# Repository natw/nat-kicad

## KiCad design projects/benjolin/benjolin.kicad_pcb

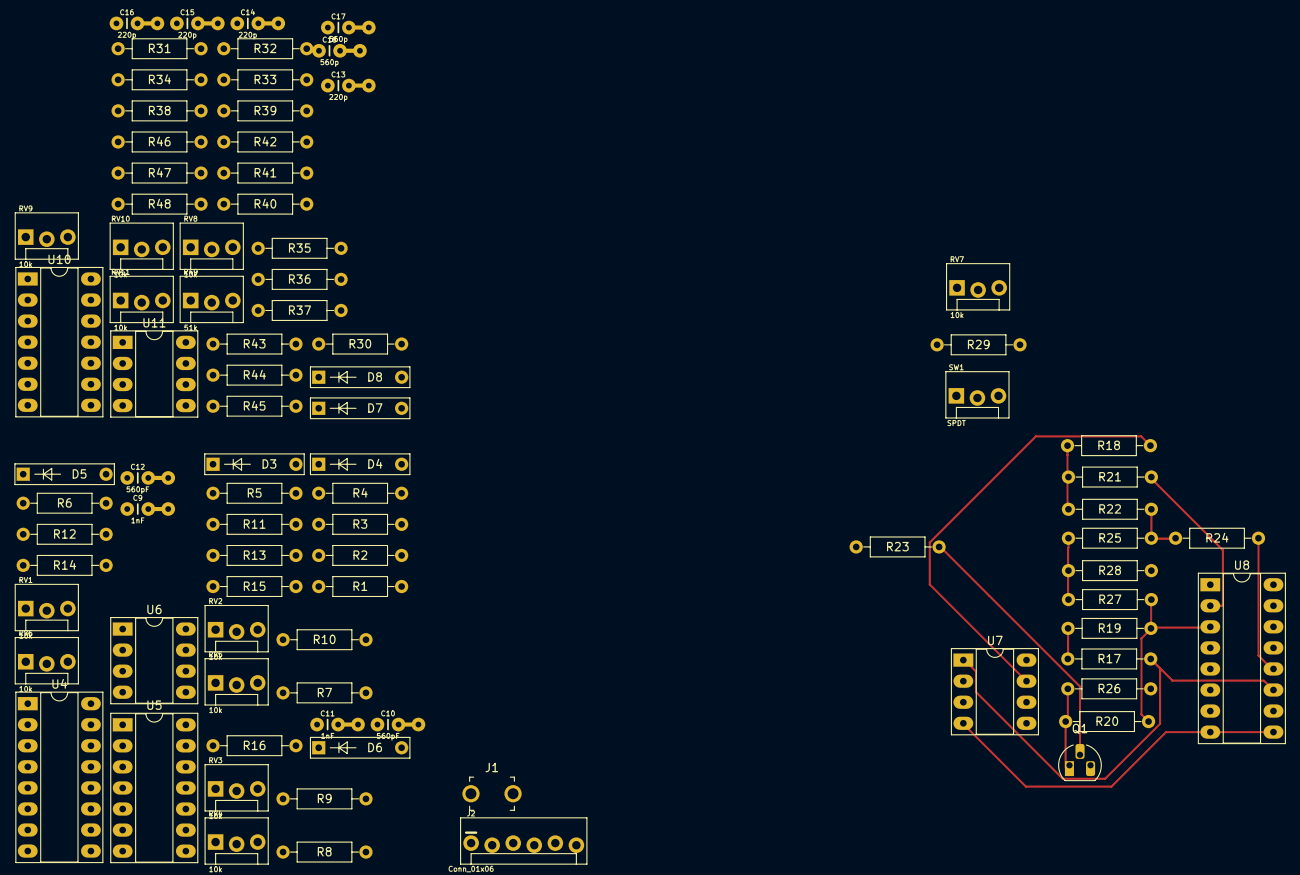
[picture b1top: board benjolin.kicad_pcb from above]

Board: 2 copper layers, 87 parts (0 on the bottom side), 62 nets.

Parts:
C9, C11: 1nF; capacitor-TH-2.54mm_5mm
C10, C12: 560pF; capacitor-TH-2.54mm_5mm
C13, C14, C15, C16: 220p; capacitor-TH-2.54mm_5mm
C17, C18: 560p; capacitor-TH-2.54mm_5mm
D3, D4, D5, D6, D7, D8: 1n4148; diode-TH
J1: LP OUT; Test_Jack_Horiz
J2: Conn_01x06; MOLEX-1X6_LOCK
Q1: BC547; TO-92_HandSolder
R1, R9, R23, R33, R44, R45: 100k; resistor-TH-10mm
R2, R8, R10, R16, R19, R20, R21, R24, R27, R28, R30, R31, R34, R35, R43: 30k; resistor-TH-10mm
R3, R11, R36, R38: 510R; resistor-TH-10mm
R4, R12, R17, R22, R25, R41: 15k; resistor-TH-10mm
R5, R13, R18, R40, R46: 10k; resistor-TH-10mm
R6, R7, R14, R15, R32, R47, R48: 51k; resistor-TH-10mm
R26, R29: 62k; resistor-TH-10mm
R37: 150k; resistor-TH-10mm
R39: 470k; resistor-TH-10mm
R42: 1k5; resistor-TH-10mm
R49: 51k; MOLEX-1X3_LOCK
RV1, RV2, RV3, RV4, RV5, RV6, RV7, RV8, RV9, RV10, RV11: 10k; MOLEX-1X3_LOCK
SW1: SPDT; MOLEX-1X3_LOCK
U4: V2164; DIP-16_W7.62mm_Socket_LongPads
U5, U10: TL074; DIP-14
U6, U7, U11: TL072; DIP-8
U8: 4021; DIP-16

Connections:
/filter/LP_OUT: C14.2, J1.1, R30.2, R39.2, U10.14
/filter/PWM_OUT: R37.2, U10.1
/filter/RUNGLER_CV: R18.2, R32.1, RV2.3, RV5.3, RV10.1, U7.7
/oscillators/OSC1_TRI_OUT: C9.2, R4.1, RV4.3, U5.7, U10.2
/oscillators/OSC2_TRI_OUT: C11.2, R12.1, RV1.3, RV9.1, U5.14, U10.3
/rungler/CLOCK_IN: R9.2, R10.2, U6.7, U8.10
/rungler/DATA_IN: R1.2, R2.2, R23.1, U6.1
/rungler/XOR_OUT: R17.2, U7.1, U8.11
GND: C10.1, C12.1, C17.1, C18.1, J2.2, J2.4, J2.5, Q1.3, R26.2, R28.2, R40.2, R42.2, RV1.1, RV2.1, RV3.1, RV4.1, RV5.1, RV6.1, RV8.1, RV9.3, RV10.3, RV11.1, U4.8, U5.3, U5.5, U5.10, U5.12, U6.2, U6.6, U7.5, U10.5, U10.10, U10.12, U11.5
unnamed: C9.1, U4.4, U5.6
unnamed: C10.2, R3.2
unnamed: C11.1, U4.5, U5.13
unnamed: C12.2, R11.2
unnamed: C13.1, U4.12, U10.9
unnamed: C13.2, C16.2, R35.1, R45.2, U10.8, U11.3
unnamed: C14.1, C15.2, U10.13
unnamed: C15.1, U4.13
unnamed: C16.1, R34.2, R36.1, R41.1, U4.10
unnamed: C17.2, R36.2
unnamed: C18.2, R38.2
unnamed: D3.1, D4.2, U5.1
unnamed: D3.2, R5.1, R6.2, R7.2, R8.2, U5.2
unnamed: D4.1, R5.2, U4.3
unnamed: D5.1, D6.2, U5.8
unnamed: D5.2, R13.1, R14.2, R15.2, R16.2, U5.9
unnamed: D6.1, R13.2, U4.6
unnamed: D7.1, D8.2, U11.7
unnamed: D7.2, R45.1, R46.1, R47.1, R48.1, R49.1, U11.6
unnamed: D8.1, R46.2, U4.11, U4.14
unnamed: Q1.1, R20.2, R26.1, U7.3
unnamed: Q1.2, R23.2, SW1.2
unnamed: R1.1, R3.1, U4.2
unnamed: R2.1, R4.2, U6.3
unnamed: R6.1, RV1.2
unnamed: R7.1, RV2.2
unnamed: R8.1, RV3.2
unnamed: R10.1, R12.2, U6.5
unnamed: R9.1, R11.1, U4.7
unnamed: R14.1, RV4.2
unnamed: R15.1, RV5.2
unnamed: R16.1, RV6.2
unnamed: R17.1, R19.2, U7.2
unnamed: R18.1, R21.2, R22.1, U7.6
unnamed: R19.1, R20.1, R27.1, U8.3
unnamed: R21.1, U8.2
unnamed: R22.2, R24.2, R25.1
unnamed: R24.1, U8.12
unnamed: R25.2, R27.2, R28.1
unnamed: R29.1, SW1.1
unnamed: R29.2, RV7.2
unnamed: R30.1, R31.1, R33.2, U10.6
unnamed: R31.2, R34.1, U10.7
unnamed: R32.2, R33.1, R37.1, R40.1, R44.1
unnamed: R35.2, R38.1, R39.1, U4.15
unnamed: R41.2, R42.1, RV8.2
unnamed: R43.1, R44.2, U11.2
unnamed: R43.2, RV8.3, U11.1
unnamed: R47.2, RV9.2
unnamed: R48.2, RV10.2
unnamed: R49.2, RV11.2
Vcc: J2.6, RV7.1, U4.16, U5.4, U6.8, U7.8, U8.16, U10.4, U11.8
Vee: J2.3, RV3.3, RV6.3, RV7.3, RV11.3, U4.9, U5.11, U6.4, U7.4, U8.8, U8.9, U10.11, U11.4

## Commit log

2019-04-18 do it
2019-05-05 add 4021
2019-05-08 more stuff around
2019-05-09 add external repos
2019-06-04 tl074 separate power
2019-06-08 updated repos
2019-06-08 makefile almost works
    doesn't refresh when lib changes
2019-06-08 bleh
2019-06-09 remove some bad ones
2019-06-09 check in lib files too
2019-06-11 not sure what a Source Symbol is, but get it out of here
2019-06-11 add interactive bom plugin
2019-06-26 new parts
2019-06-26 update libs
2019-06-26 opamp changes
2019-06-27 asdf
2019-06-27 add HierPlace plugin
2019-07-25 mounting hole footprint
2019-09-21 work on build script
2019-09-21 footprints, mostly headers
2019-09-21 regulators, I think
2019-09-21 update externals
2019-09-21 script almost seems to work
2019-09-21 update kicad repos
2019-09-21 some janky string escaping
2019-09-21 updated tables
2019-09-21 disable a whole bunch I don't need
2019-09-25 some new symbols and such
2019-11-15 update external libs
2019-11-15 update tables
2020-04-04 i dunno
2021-12-28 add benjolin
2022-03-05 new symbol lib?
2022-03-05 dunno
2022-03-19 update kicad libs with gitlab urls
2022-05-11 add a bunch of spice models
2022-05-11 add some pedal projects
2022-06-24 do I actually want projects here?
2022-08-13 update library script for new format and better dupe handling
2022-08-13 it's a dual benjolin
